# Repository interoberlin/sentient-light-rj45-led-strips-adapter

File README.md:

# sentient-light-rj45-led-strips-adapter

The adapter receives four data signals via an off-the-shelf RJ-45 ethernet socket
and routes them to a 1x5-pin header as well as to LED strip solder pads.
The adapter is intended for usage with strips of addressable LEDs (e.g. WS2812 or SK6812).

## Original design goals

* The 1x5-pin header must match the pin layout previously used in this project:
  * https://github.com/interoberlin/Baumhaus-Tree-Adapter
* The RJ-45 socket pins assignment must match the one used in this project:
  * https://github.com/interoberlin/sentient-light-fpga-rj45-adapter
* The PCB should have holes suitable for (wall) mounting.
* It should be possible to attach a 5V supply to the board, e.g. via USB, screw socket or barrel jack socket.
* A high current-capable diode should protect against incorrect supply voltage polarization.
* One LED of the RJ-45 socket should announce the presence of the 5V supply voltage.
* The second LED should light up, when data is received on one of the four signal lines.
* Footprints should be present for one or more 5V LDOs (depending on the required LED current).

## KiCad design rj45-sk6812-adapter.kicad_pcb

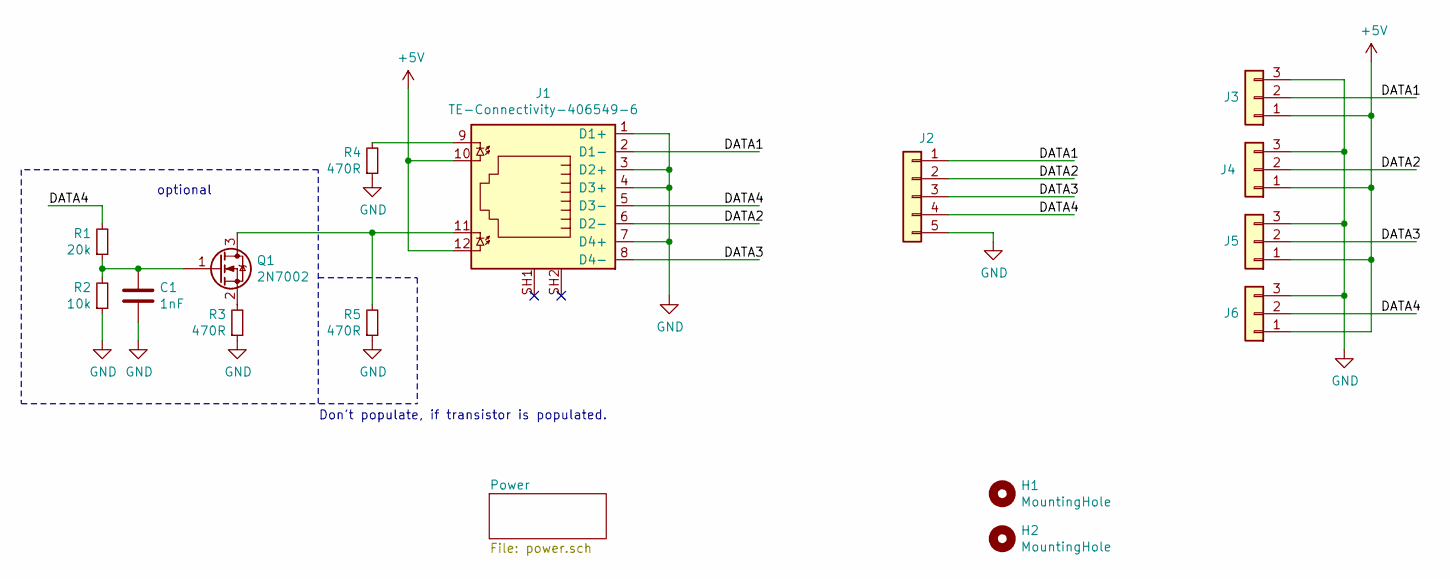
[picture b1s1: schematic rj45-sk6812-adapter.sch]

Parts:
C1: 1nF; C_0805_2012Metric_Pad1.15x1.40mm_HandSolder
H1, H2: MountingHole; MountingHole_4.5mm
J1: TE-Connectivity-406549-6
J2: Conn_01x05; PinHeader_1x05_P2.54mm_Vertical
J3, J4, J5, J6: Conn_01x03; WS6812-SK6812
Q1: 2N7002; SOT-23
R1: 20k; R_0805_2012Metric_Pad1.15x1.40mm_HandSolder
R2: 10k; R_0805_2012Metric_Pad1.15x1.40mm_HandSolder
R3, R4, R5: 470R; R_0805_2012Metric_Pad1.15x1.40mm_HandSolder

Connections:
+5V: J1.10, J1.12, J3.1, J4.1, J5.1, J6.1; also elsewhere on the board
/DATA1: J1.2 (D1-), J2.1, J3.2
/DATA2: J1.6 (D2-), J2.2, J4.2
/DATA3: J1.8 (D4-), J2.3, J5.2
/DATA4: J1.5 (D3-), J2.4, J6.2, R1.2
GND: C1.2, J1.1 (D1+), J1.3 (D2+), J1.4 (D3+), J1.7 (D4+), J2.5, J3.3, J4.3, J5.3, J6.3, R2.1, R3.1, R4.1, R5.1; also elsewhere on the board
unnamed: C1.1, Q1.1 (G), R1.1, R2.2
unnamed: J1.9, R4.2
unnamed: J1.11, Q1.3 (D), R5.2
unnamed: Q1.2 (S), R3.2

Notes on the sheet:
optional
Don't populate, if transistor is populated.

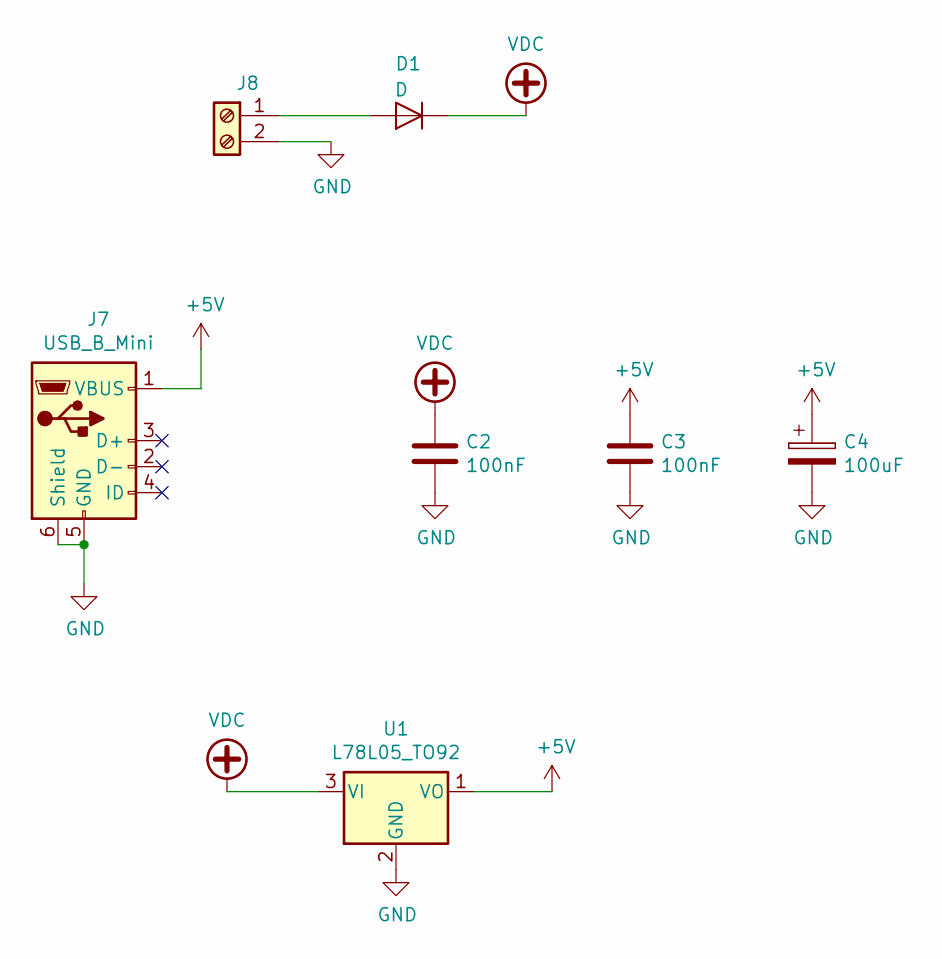
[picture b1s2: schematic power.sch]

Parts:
C2, C3: 100nF; C_0805_2012Metric_Pad1.15x1.40mm_HandSolder
C4: 100uF; CP_Radial_D8.0mm_P3.80mm
D1: D; D_MELF_Handsoldering
J7: USB_B_Mini; USB_Mini-B_Lumberg_2486_01_Horizontal
J8: Screw_Terminal_01x02; TerminalBlock_bornier-2_P5.08mm
U1: L78L05_TO92; TO-92_Inline

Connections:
+5V: C3.1, C4.1, J7.1 (VBUS), U1.1 (VO); also elsewhere on the board
GND: C2.2, C3.2, C4.2, J7.5 (GND), J7.6 (Shield), J8.2, U1.2 (GND); also elsewhere on the board
unnamed: D1.2 (A), J8.1
VDC: C2.1, D1.1 (K), U1.3 (VI)

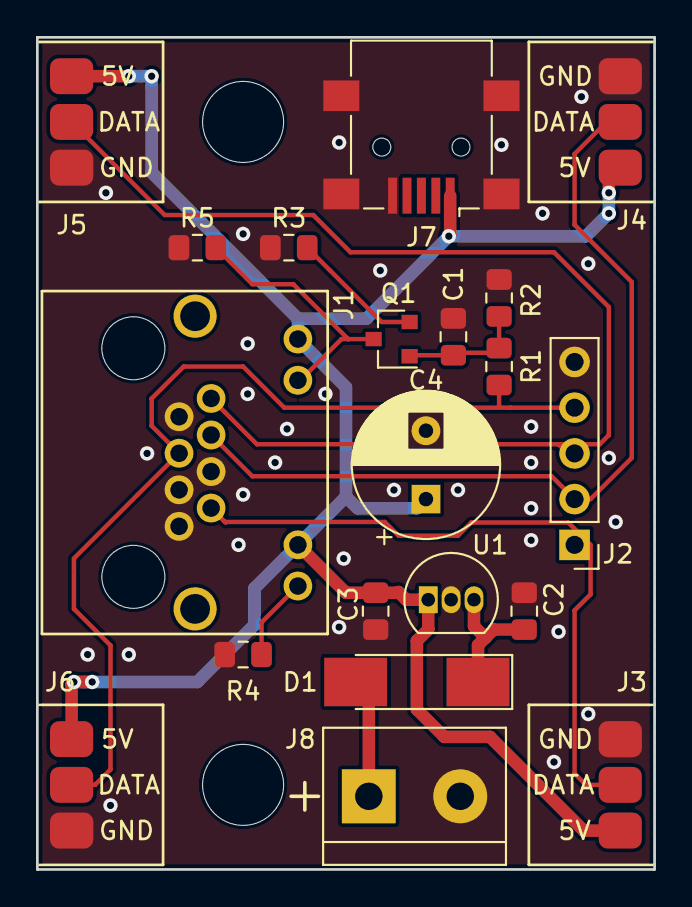
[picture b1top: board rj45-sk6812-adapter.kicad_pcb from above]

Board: 2 copper layers, 34.3 x 46.2 mm, 22 parts (0 on the bottom side), 12 nets.

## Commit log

2018-10-25 Completed schematic
2018-10-25 Added mini-USB socket
2018-10-25 Finished layouting
2018-11-27 Added my KiCad libraries as submodule
2018-11-27 Using the correct RJ-45 socket
    Added LED resistor and capacitor
2018-12-02 Finished layouting
    Added an optional circuit to blink an LED during data transmission
    and a diode protected and 5V regulated power supply connector.
2018-12-02 Exported fabrication files
2018-12-02 Added capacitor to stabilize the LEDs' 5V supply
2019-03-09 Added 3d model screenshot
2019-03-09 Include model.jpg
